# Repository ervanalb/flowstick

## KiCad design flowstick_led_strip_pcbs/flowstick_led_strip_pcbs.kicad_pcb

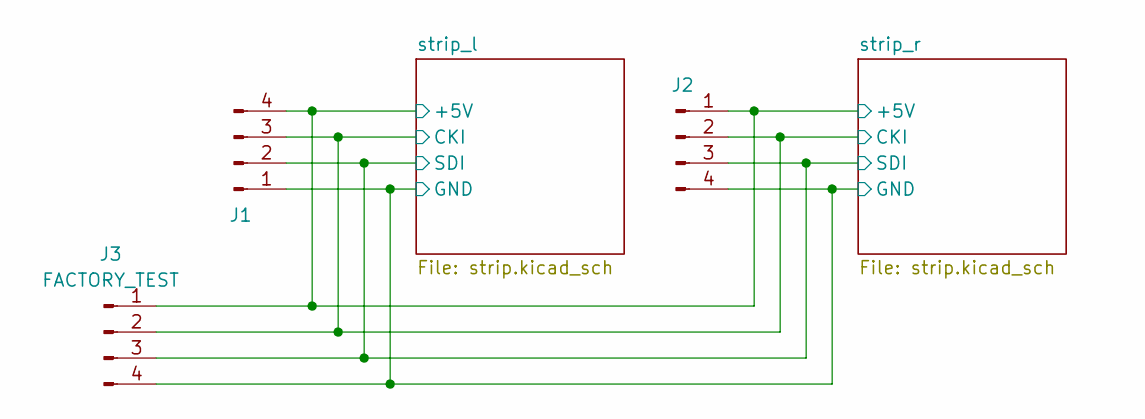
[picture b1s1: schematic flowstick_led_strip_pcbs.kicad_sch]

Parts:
J1, J2: LED; quad_b2b_pad
J3: FACTORY_TEST; PinHeader_1x04_P2.54mm_Vertical

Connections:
/strip_l/+5V: J1.4, J2.1, J3.1; also elsewhere on the board
/strip_l/CKI: J1.3, J2.2, J3.2; also elsewhere on the board
/strip_l/GND: J1.1, J2.4, J3.4; also elsewhere on the board
/strip_l/SDI: J1.2, J2.3, J3.3; also elsewhere on the board

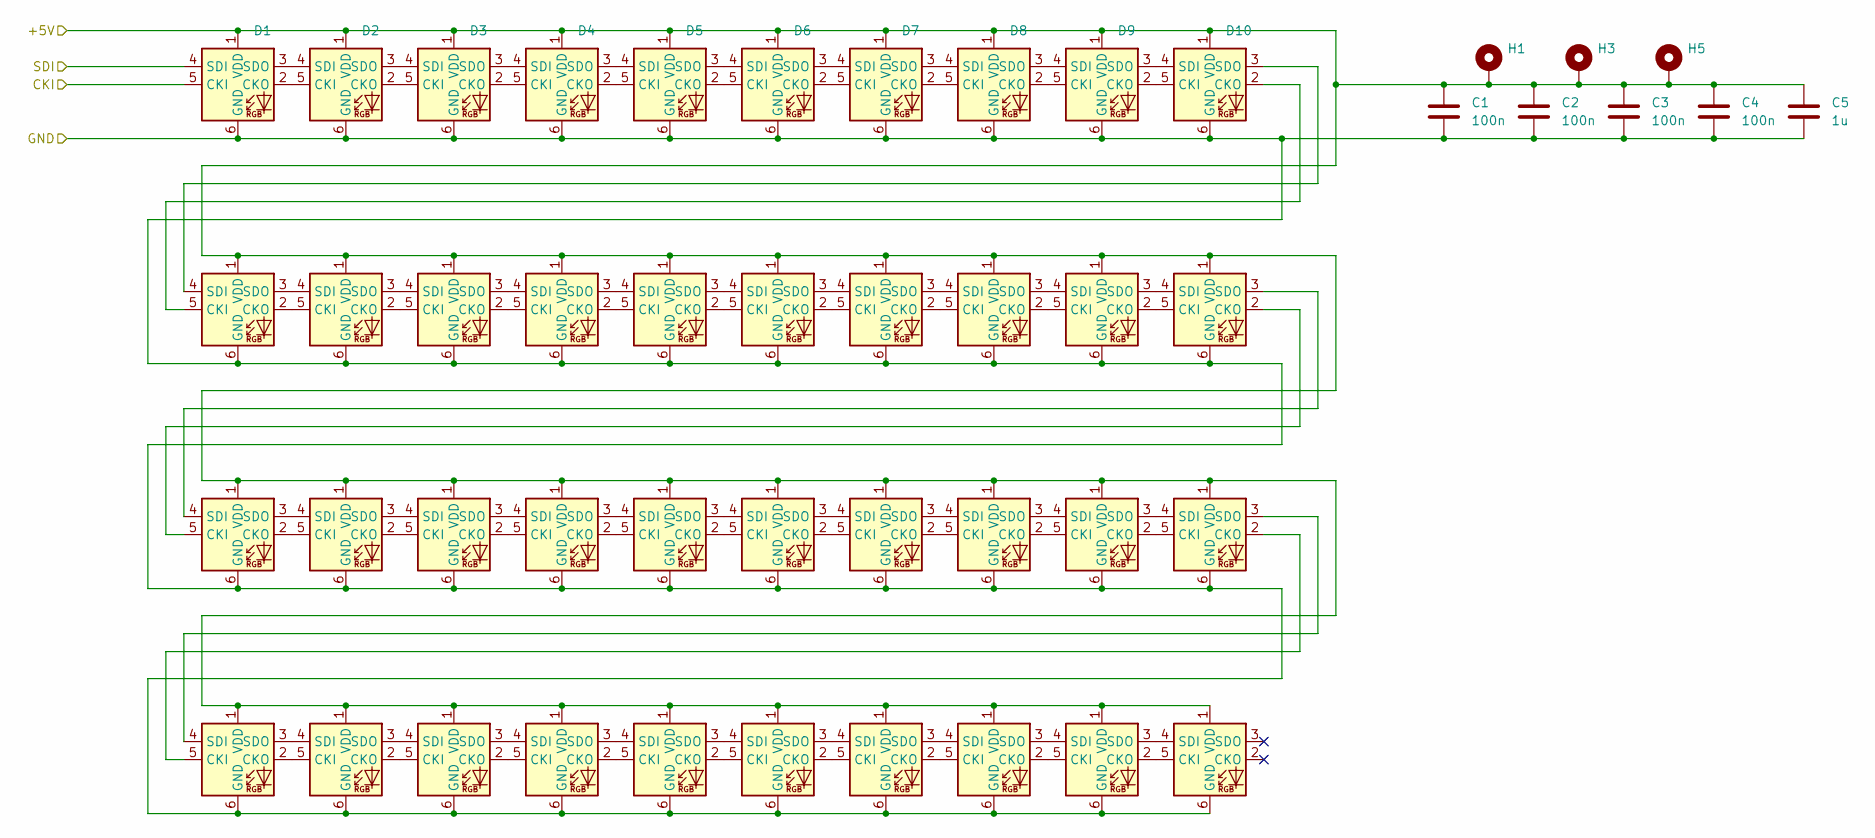
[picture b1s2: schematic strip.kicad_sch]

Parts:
C1, C2, C3, C4: 100n; C_0603_1608Metric
C5: 1u; C_0603_1608Metric
D1, D2, D3, D4, D5, D6, D7, D8, D9, D10, D11, D12, D13, D14, D15, D16, D17, D18, D19, D20, D21, D22, D23, D24, D25, D26, D27, D28, D29, D30, D31, D32, D33, D34, D35, D36, D37, D38, D39, D40: APA102-2020; LED-APA102-2020-6_90deg
H1, H3, H5: MountingHole_Pad; single_b2b_pad_doublewide

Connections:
/strip_l/+5V: C1.1, C2.1, C3.1, C4.1, C5.1, D1.1 (VDD), D2.1 (VDD), D3.1 (VDD), D4.1 (VDD), D5.1 (VDD), D6.1 (VDD), D7.1 (VDD), D8.1 (VDD), D9.1 (VDD), D10.1 (VDD), D11.1 (VDD), D12.1 (VDD), D13.1 (VDD), D14.1 (VDD), D15.1 (VDD), D16.1 (VDD), D17.1 (VDD), D18.1 (VDD), D19.1 (VDD), D20.1 (VDD), D21.1 (VDD), D22.1 (VDD), D23.1 (VDD), D24.1 (VDD), D25.1 (VDD), D26.1 (VDD), D27.1 (VDD), D28.1 (VDD), D29.1 (VDD), D30.1 (VDD), D31.1 (VDD), D32.1 (VDD), D33.1 (VDD), D34.1 (VDD), D35.1 (VDD), D36.1 (VDD), D37.1 (VDD), D38.1 (VDD), D39.1 (VDD), D40.1 (VDD), H1.1, H3.1, H5.1; also elsewhere on the board
/strip_l/CKI: D1.5 (CKI); also elsewhere on the board
/strip_l/GND: C1.2, C2.2, C3.2, C4.2, C5.2, D1.6 (GND), D2.6 (GND), D3.6 (GND), D4.6 (GND), D5.6 (GND), D6.6 (GND), D7.6 (GND), D8.6 (GND), D9.6 (GND), D10.6 (GND), D11.6 (GND), D12.6 (GND), D13.6 (GND), D14.6 (GND), D15.6 (GND), D16.6 (GND), D17.6 (GND), D18.6 (GND), D19.6 (GND), D20.6 (GND), D21.6 (GND), D22.6 (GND), D23.6 (GND), D24.6 (GND), D25.6 (GND), D26.6 (GND), D27.6 (GND), D28.6 (GND), D29.6 (GND), D30.6 (GND), D31.6 (GND), D32.6 (GND), D33.6 (GND), D34.6 (GND), D35.6 (GND), D36.6 (GND), D37.6 (GND), D38.6 (GND), D39.6 (GND), D40.6 (GND); also elsewhere on the board
/strip_l/SDI: D1.4 (SDI); also elsewhere on the board
unnamed: D1.2 (CKO), D2.5 (CKI)
unnamed: D1.3 (SDO), D2.4 (SDI)
unnamed: D2.2 (CKO), D3.5 (CKI)
unnamed: D2.3 (SDO), D3.4 (SDI)
unnamed: D3.2 (CKO), D4.5 (CKI)
unnamed: D3.3 (SDO), D4.4 (SDI)
unnamed: D4.2 (CKO), D5.5 (CKI)
unnamed: D4.3 (SDO), D5.4 (SDI)
unnamed: D5.2 (CKO), D6.5 (CKI)
unnamed: D5.3 (SDO), D6.4 (SDI)
unnamed: D6.2 (CKO), D7.5 (CKI)
unnamed: D6.3 (SDO), D7.4 (SDI)
unnamed: D7.2 (CKO), D8.5 (CKI)
unnamed: D7.3 (SDO), D8.4 (SDI)
unnamed: D8.2 (CKO), D9.5 (CKI)
unnamed: D8.3 (SDO), D9.4 (SDI)
unnamed: D9.2 (CKO), D10.5 (CKI)
unnamed: D10.2 (CKO), D11.5 (CKI)
unnamed: D9.3 (SDO), D10.4 (SDI)
unnamed: D10.3 (SDO), D11.4 (SDI)
unnamed: D11.2 (CKO), D12.5 (CKI)
unnamed: D11.3 (SDO), D12.4 (SDI)
unnamed: D12.2 (CKO), D13.5 (CKI)
unnamed: D12.3 (SDO), D13.4 (SDI)
unnamed: D13.2 (CKO), D14.5 (CKI)
unnamed: D13.3 (SDO), D14.4 (SDI)
unnamed: D14.2 (CKO), D15.5 (CKI)
unnamed: D14.3 (SDO), D15.4 (SDI)
unnamed: D15.2 (CKO), D16.5 (CKI)
unnamed: D15.3 (SDO), D16.4 (SDI)
unnamed: D16.2 (CKO), D17.5 (CKI)
unnamed: D16.3 (SDO), D17.4 (SDI)
unnamed: D17.2 (CKO), D18.5 (CKI)
unnamed: D17.3 (SDO), D18.4 (SDI)
unnamed: D18.2 (CKO), D19.5 (CKI)
unnamed: D18.3 (SDO), D19.4 (SDI)
unnamed: D19.2 (CKO), D20.5 (CKI)
unnamed: D19.3 (SDO), D20.4 (SDI)
unnamed: D20.2 (CKO), D21.5 (CKI)
unnamed: D20.3 (SDO), D21.4 (SDI)
unnamed: D21.2 (CKO), D22.5 (CKI)
unnamed: D21.3 (SDO), D22.4 (SDI)
unnamed: D22.2 (CKO), D23.5 (CKI)
unnamed: D22.3 (SDO), D23.4 (SDI)
unnamed: D23.2 (CKO), D24.5 (CKI)
unnamed: D23.3 (SDO), D24.4 (SDI)
unnamed: D24.2 (CKO), D25.5 (CKI)
unnamed: D24.3 (SDO), D25.4 (SDI)
unnamed: D25.2 (CKO), D26.5 (CKI)
unnamed: D25.3 (SDO), D26.4 (SDI)
unnamed: D26.2 (CKO), D27.5 (CKI)
unnamed: D26.3 (SDO), D27.4 (SDI)
unnamed: D27.2 (CKO), D28.5 (CKI)
unnamed: D27.3 (SDO), D28.4 (SDI)
unnamed: D28.2 (CKO), D29.5 (CKI)
unnamed: D28.3 (SDO), D29.4 (SDI)
unnamed: D29.2 (CKO), D30.5 (CKI)
unnamed: D29.3 (SDO), D30.4 (SDI)
unnamed: D30.2 (CKO), D31.5 (CKI)
unnamed: D30.3 (SDO), D31.4 (SDI)
unnamed: D31.2 (CKO), D32.5 (CKI)
unnamed: D31.3 (SDO), D32.4 (SDI)
unnamed: D32.2 (CKO), D33.5 (CKI)
unnamed: D32.3 (SDO), D33.4 (SDI)
unnamed: D33.2 (CKO), D34.5 (CKI)
unnamed: D33.3 (SDO), D34.4 (SDI)
unnamed: D34.2 (CKO), D35.5 (CKI)
unnamed: D34.3 (SDO), D35.4 (SDI)
unnamed: D35.2 (CKO), D36.5 (CKI)
unnamed: D35.3 (SDO), D36.4 (SDI)
unnamed: D36.2 (CKO), D37.5 (CKI)
unnamed: D36.3 (SDO), D37.4 (SDI)
unnamed: D37.2 (CKO), D38.5 (CKI)
unnamed: D37.3 (SDO), D38.4 (SDI)
unnamed: D38.2 (CKO), D39.5 (CKI)
unnamed: D38.3 (SDO), D39.4 (SDI)
unnamed: D39.2 (CKO), D40.5 (CKI)
unnamed: D39.3 (SDO), D40.4 (SDI)

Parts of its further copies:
C6, C7, C8, C9: 100n; C_0603_1608Metric
C10: 1u; C_0603_1608Metric
D41, D42, D43, D44, D45, D46, D47, D48, D49, D50, D51, D52, D53, D54, D55, D56, D57, D58, D59, D60, D61, D62, D63, D64, D65, D66, D67, D68, D69, D70, D71, D72, D73, D74, D75, D76, D77, D78, D79, D80: APA102-2020; LED-APA102-2020-6_90deg
H2, H4, H6: MountingHole_Pad; single_b2b_pad_doublewide

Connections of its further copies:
/strip_l/+5V: C6.1, C7.1, C8.1, C9.1, C10.1, D41.1 (VDD), D42.1 (VDD), D43.1 (VDD), D44.1 (VDD), D45.1 (VDD), D46.1 (VDD), D47.1 (VDD), D48.1 (VDD), D49.1 (VDD), D50.1 (VDD), D51.1 (VDD), D52.1 (VDD), D53.1 (VDD), D54.1 (VDD), D55.1 (VDD), D56.1 (VDD), D57.1 (VDD), D58.1 (VDD), D59.1 (VDD), D60.1 (VDD), D61.1 (VDD), D62.1 (VDD), D63.1 (VDD), D64.1 (VDD), D65.1 (VDD), D66.1 (VDD), D67.1 (VDD), D68.1 (VDD), D69.1 (VDD), D70.1 (VDD), D71.1 (VDD), D72.1 (VDD), D73.1 (VDD), D74.1 (VDD), D75.1 (VDD), D76.1 (VDD), D77.1 (VDD), D78.1 (VDD), D79.1 (VDD), D80.1 (VDD), H2.1, H4.1, H6.1; also elsewhere on the board
/strip_l/CKI: D41.5 (CKI); also elsewhere on the board
/strip_l/GND: C6.2, C7.2, C8.2, C9.2, C10.2, D41.6 (GND), D42.6 (GND), D43.6 (GND), D44.6 (GND), D45.6 (GND), D46.6 (GND), D47.6 (GND), D48.6 (GND), D49.6 (GND), D50.6 (GND), D51.6 (GND), D52.6 (GND), D53.6 (GND), D54.6 (GND), D55.6 (GND), D56.6 (GND), D57.6 (GND), D58.6 (GND), D59.6 (GND), D60.6 (GND), D61.6 (GND), D62.6 (GND), D63.6 (GND), D64.6 (GND), D65.6 (GND), D66.6 (GND), D67.6 (GND), D68.6 (GND), D69.6 (GND), D70.6 (GND), D71.6 (GND), D72.6 (GND), D73.6 (GND), D74.6 (GND), D75.6 (GND), D76.6 (GND), D77.6 (GND), D78.6 (GND), D79.6 (GND), D80.6 (GND); also elsewhere on the board
/strip_l/SDI: D41.4 (SDI); also elsewhere on the board
unnamed: D41.2 (CKO), D42.5 (CKI)
unnamed: D41.3 (SDO), D42.4 (SDI)
unnamed: D42.2 (CKO), D43.5 (CKI)
unnamed: D42.3 (SDO), D43.4 (SDI)
unnamed: D43.2 (CKO), D44.5 (CKI)
unnamed: D43.3 (SDO), D44.4 (SDI)
unnamed: D44.2 (CKO), D45.5 (CKI)
unnamed: D44.3 (SDO), D45.4 (SDI)
unnamed: D45.2 (CKO), D46.5 (CKI)
unnamed: D45.3 (SDO), D46.4 (SDI)
unnamed: D46.2 (CKO), D47.5 (CKI)
unnamed: D46.3 (SDO), D47.4 (SDI)
unnamed: D47.2 (CKO), D48.5 (CKI)
unnamed: D47.3 (SDO), D48.4 (SDI)
unnamed: D48.2 (CKO), D49.5 (CKI)
unnamed: D48.3 (SDO), D49.4 (SDI)
unnamed: D49.2 (CKO), D50.5 (CKI)
unnamed: D49.3 (SDO), D50.4 (SDI)
unnamed: D50.2 (CKO), D51.5 (CKI)
unnamed: D50.3 (SDO), D51.4 (SDI)
unnamed: D51.2 (CKO), D52.5 (CKI)
unnamed: D51.3 (SDO), D52.4 (SDI)
unnamed: D52.2 (CKO), D53.5 (CKI)
unnamed: D52.3 (SDO), D53.4 (SDI)
unnamed: D53.2 (CKO), D54.5 (CKI)
unnamed: D53.3 (SDO), D54.4 (SDI)
unnamed: D54.2 (CKO), D55.5 (CKI)
unnamed: D54.3 (SDO), D55.4 (SDI)
unnamed: D55.2 (CKO), D56.5 (CKI)
unnamed: D55.3 (SDO), D56.4 (SDI)
unnamed: D56.2 (CKO), D57.5 (CKI)
unnamed: D56.3 (SDO), D57.4 (SDI)
unnamed: D57.2 (CKO), D58.5 (CKI)
unnamed: D57.3 (SDO), D58.4 (SDI)
unnamed: D58.2 (CKO), D59.5 (CKI)
unnamed: D58.3 (SDO), D59.4 (SDI)
unnamed: D59.2 (CKO), D60.5 (CKI)
unnamed: D59.3 (SDO), D60.4 (SDI)
unnamed: D60.2 (CKO), D61.5 (CKI)
unnamed: D60.3 (SDO), D61.4 (SDI)
unnamed: D61.2 (CKO), D62.5 (CKI)
unnamed: D61.3 (SDO), D62.4 (SDI)
unnamed: D62.2 (CKO), D63.5 (CKI)
unnamed: D62.3 (SDO), D63.4 (SDI)
unnamed: D63.2 (CKO), D64.5 (CKI)
unnamed: D63.3 (SDO), D64.4 (SDI)
unnamed: D64.2 (CKO), D65.5 (CKI)
unnamed: D64.3 (SDO), D65.4 (SDI)
unnamed: D65.2 (CKO), D66.5 (CKI)
unnamed: D65.3 (SDO), D66.4 (SDI)
unnamed: D66.2 (CKO), D67.5 (CKI)
unnamed: D66.3 (SDO), D67.4 (SDI)
unnamed: D67.2 (CKO), D68.5 (CKI)
unnamed: D67.3 (SDO), D68.4 (SDI)
unnamed: D68.2 (CKO), D69.5 (CKI)
unnamed: D68.3 (SDO), D69.4 (SDI)
unnamed: D69.2 (CKO), D70.5 (CKI)
unnamed: D69.3 (SDO), D70.4 (SDI)
unnamed: D70.2 (CKO), D71.5 (CKI)
unnamed: D70.3 (SDO), D71.4 (SDI)
unnamed: D71.2 (CKO), D72.5 (CKI)
unnamed: D71.3 (SDO), D72.4 (SDI)
unnamed: D72.2 (CKO), D73.5 (CKI)
unnamed: D72.3 (SDO), D73.4 (SDI)
unnamed: D73.2 (CKO), D74.5 (CKI)
unnamed: D73.3 (SDO), D74.4 (SDI)
unnamed: D74.2 (CKO), D75.5 (CKI)
unnamed: D74.3 (SDO), D75.4 (SDI)
unnamed: D75.2 (CKO), D76.5 (CKI)
unnamed: D75.3 (SDO), D76.4 (SDI)
unnamed: D76.2 (CKO), D77.5 (CKI)
unnamed: D76.3 (SDO), D77.4 (SDI)
unnamed: D77.2 (CKO), D78.5 (CKI)
unnamed: D77.3 (SDO), D78.4 (SDI)
unnamed: D78.2 (CKO), D79.5 (CKI)
unnamed: D78.3 (SDO), D79.4 (SDI)
unnamed: D79.2 (CKO), D80.5 (CKI)
unnamed: D79.3 (SDO), D80.4 (SDI)

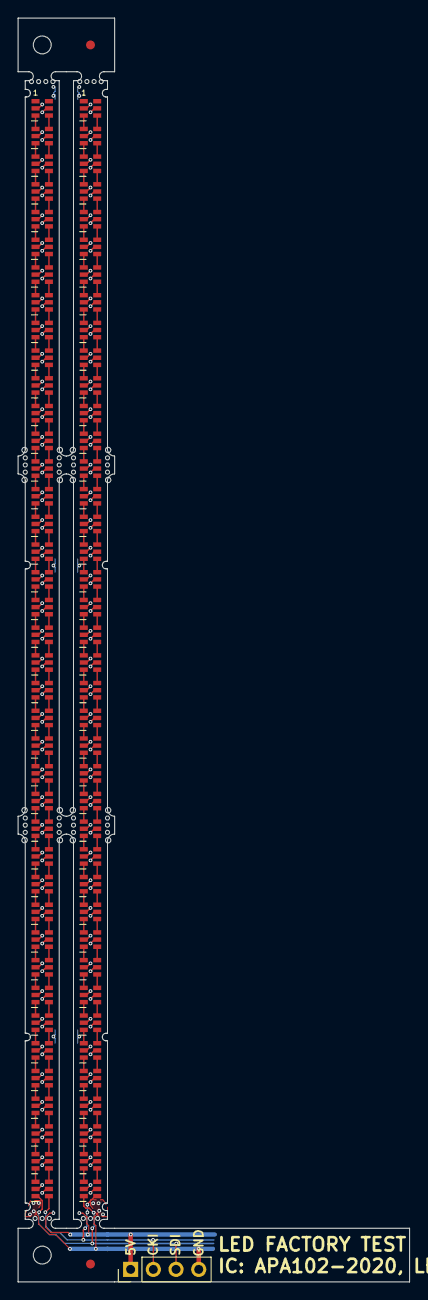
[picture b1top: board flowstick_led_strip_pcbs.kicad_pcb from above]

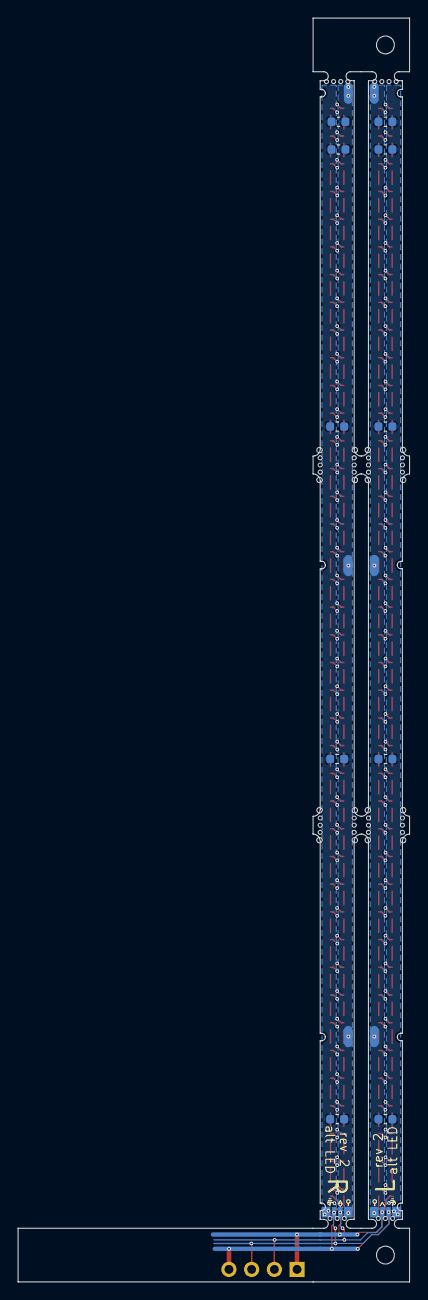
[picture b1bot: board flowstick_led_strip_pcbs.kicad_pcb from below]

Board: 2 copper layers, 43.8 x 141.4 mm, 99 parts (18 on the bottom side), 160 nets.

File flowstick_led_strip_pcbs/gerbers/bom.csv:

Designator,Quantity,Value,Footprint,Manufacturer,Part Number,JLCPCB Part #
"C1,C2,C3,C4,C6,C7,C8,C9",64,100n,Capacitor_SMD:C_0603_1608Metric,,,C14663
"C5,C10",16,1u,Capacitor_SMD:C_0603_1608Metric,,,C106248
"D1,D2,D3,D4,D5,D6,D7,D8,D9,D10,D11,D12,D13,D14,D15,D16,D17,D18,D19,D20,D21,D22,D23,D24,D25,D26,D27,D28,D29,D30,D31,D32,D33,D34,D35,D36,D37,D38,D39,D40,D41,D42,D43,D44,D45,D46,D47,D48,D49,D50,D51,D52,D53,D54,D55,D56,D57,D58,D59,D60,D61,D62,D63,D64,D65,D66,D67,D68,D69,D70,D71,D72,D73,D74,D75,D76,D77,D78,D79,D80",640,APA102-2020,LED_SMD:LED-APA102-2020,APA Electronics,APA102-2020,C22439302

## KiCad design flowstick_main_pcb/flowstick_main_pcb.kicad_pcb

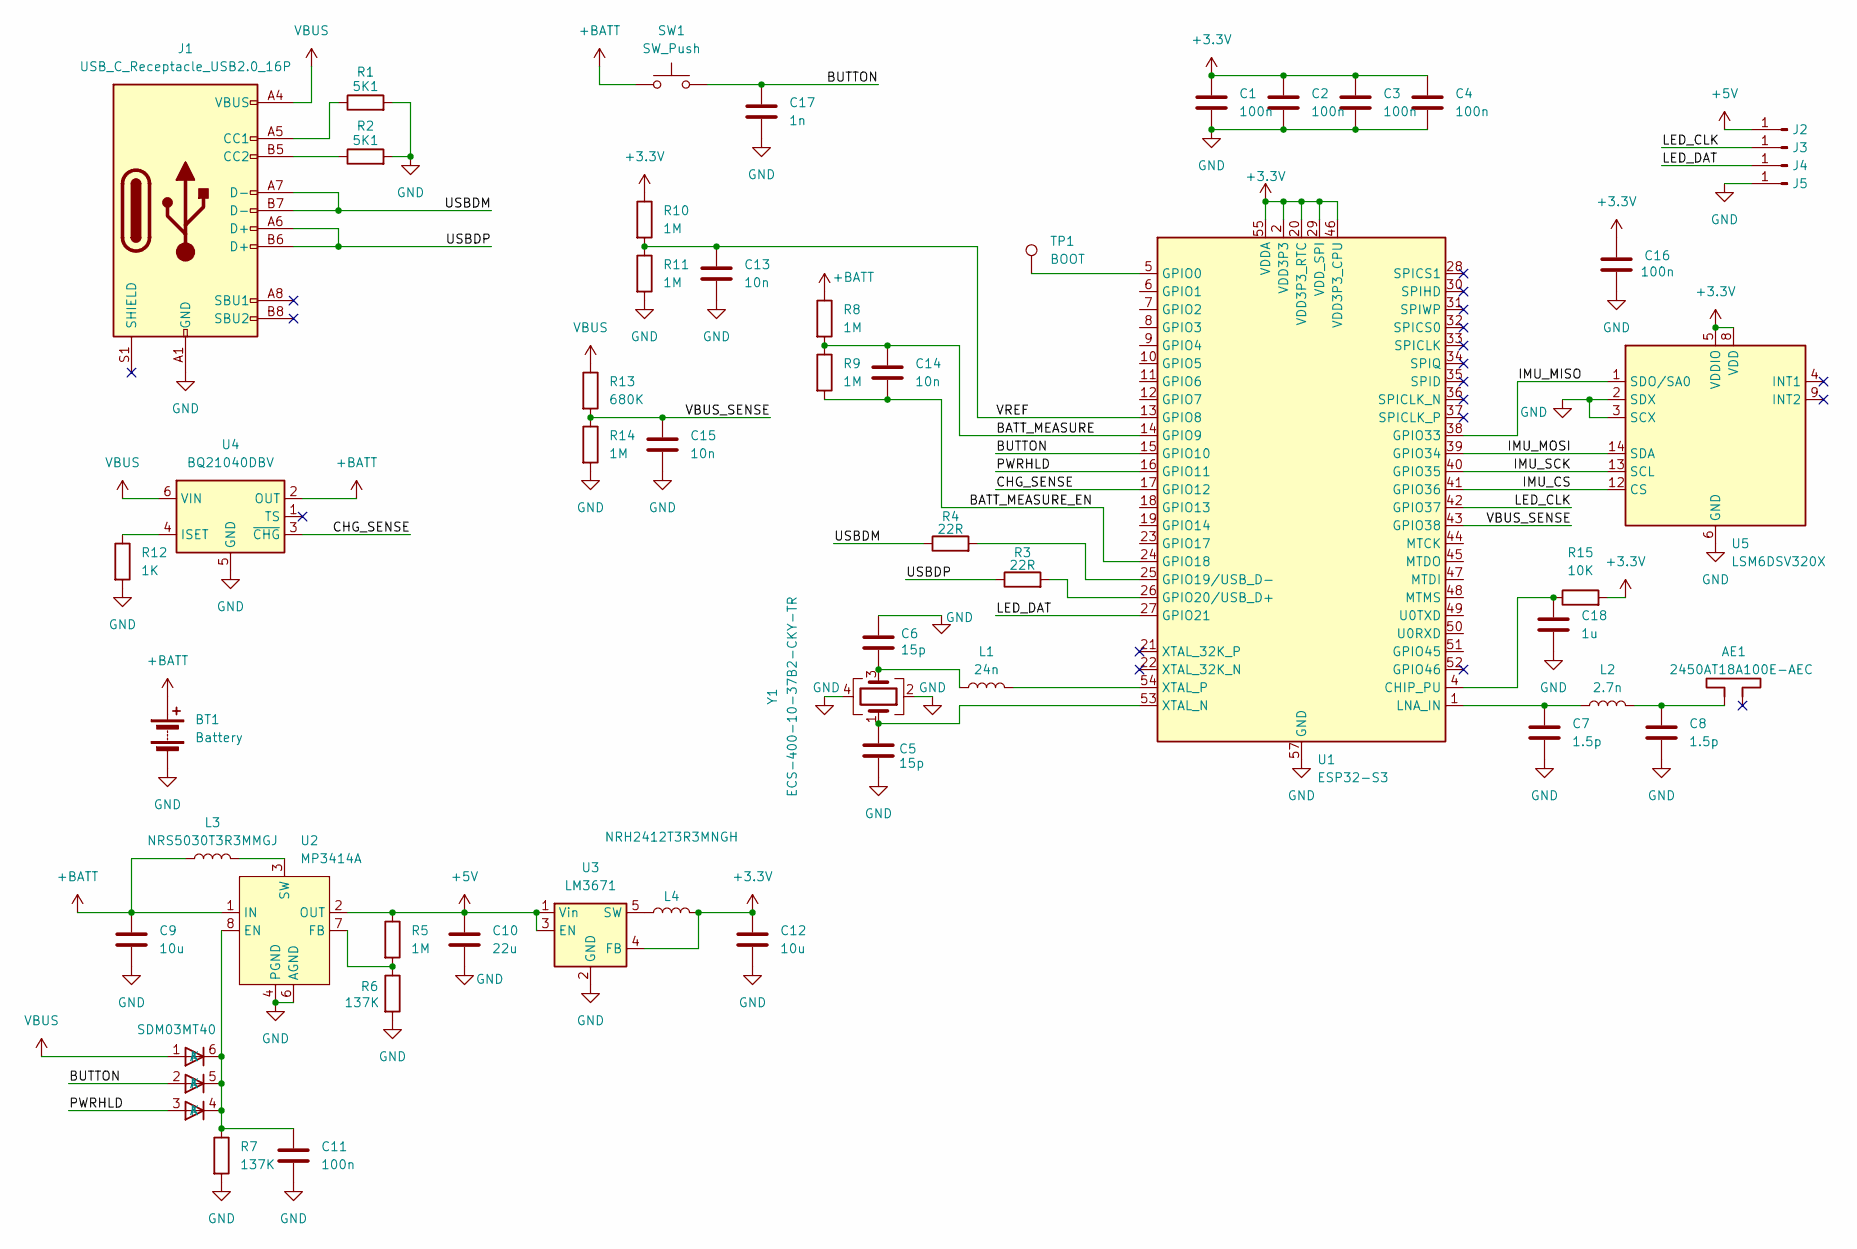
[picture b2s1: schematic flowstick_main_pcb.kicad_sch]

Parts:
AE1: 2450AT18A100E-AEC; R_1206_3216Metric
BT1: Battery; PinHeader_1x02_P2.54mm_Vertical
C1, C2, C3, C4, C16: 100n; C_0402_1005Metric
C5, C6: 15p; C_0201_0603Metric
C7, C8: 1.5p; C_0201_0603Metric
C9, C12: 10u; C_1206_3216Metric
C10: 22u; C_1206_3216Metric
C11: 100n; C_0201_0603Metric
C13, C14, C15: 10n; C_0201_0603Metric
C17: 1n; C_0201_0603Metric
C18: 1u; C_0201_0603Metric
D1: SDM03MT40; SOT-23-6
J1: USB_C_Receptacle_USB2.0_16P; USB_C_Receptacle_GCT_USB4105-xx-A_16P_TopMnt_Horizontal
J2, J3, J4, J5: Conn_01x01_Pin; Untitled
L1: 24n; L_0201_0603Metric
L2: 2.7n; L_0201_0603Metric
L3: NRS5030T3R3MMGJ; L_Taiyo-Yuden_NR-50xx
L4: NRH2412T3R3MNGH; L_Taiyo-Yuden_NR-24xx
R1, R2: 5K1; C_0201_0603Metric
R3, R4: 22R; C_0201_0603Metric
R5, R8, R9, R10, R11, R14: 1M; C_0201_0603Metric
R6, R7: 137K; C_0201_0603Metric
R12: 1K; C_0201_0603Metric
R13: 680K; C_0201_0603Metric
R15: 10K; R_0201_0603Metric
SW1: SW_Push; SW_SPST_EVQP7C
TP1: BOOT; TestPoint_Pad_D1.0mm
U1: ESP32-S3; QFN-56-1EP_7x7mm_P0.4mm_EP4x4mm
U2: MP3414A; TSOT-23-8
U3: LM3671; TSOT-23-5
U4: BQ21040DBV; SOT-23-6
U5: LSM6DSV320X; LGA-14_3x2.5mm_P0.5mm_LayoutBorder3x4y
Y1: ECS-400-10-37B2-CKY-TR; Crystal_SMD_2016-4Pin_2.0x1.6mm

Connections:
+3.3V: C1.1, C2.1, C3.1, C4.1, C12.1, C16.1, L4.2, R10.1, R15.2, U1.2 (VDD3P3), U1.3 (VDD3P3), U1.20 (VDD3P3_RTC), U1.29 (VDD_SPI), U1.46 (VDD3P3_CPU), U1.55 (VDDA), U1.56 (VDDA), U3.4 (FB), U5.5 (VDDIO), U5.8 (VDD)
+5V: C10.1, J2.1, R5.1, U2.2 (OUT), U3.1 (Vin), U3.3 (EN)
+BATT: BT1.1 (+), C9.1, L3.1, R8.1, SW1.1, U2.1 (IN), U4.2 (OUT)
/BATT_MEASURE: C14.1, R8.2, R9.1, U1.14 (GPIO9)
/BATT_MEASURE_EN: C14.2, R9.2, U1.24 (GPIO18)
/BUTTON: C17.1, D1.2 (A), SW1.2, U1.15 (GPIO10)
/CHG_SENSE: U1.17 (GPIO12), U4.3 (~CHG)
/IMU_CS: U1.41 (GPIO36), U5.12 (CS)
/IMU_PICO: U1.38 (GPIO33), U5.1 (SDO/SA0)
/IMU_POCI: U1.39 (GPIO34), U5.14 (SDA)
/IMU_SCK: U1.40 (GPIO35), U5.13 (SCL)
/LED_CLK: J3.1, U1.42 (GPIO37)
/LED_DAT: J4.1, U1.27 (GPIO21)
/PWRHLD: D1.3 (A), U1.16 (GPIO11)
/USBDM: J1.A7 (D-), J1.B7 (D-), R4.1
/USBDP: J1.A6 (D+), J1.B6 (D+), R3.1
/VBUS_SENSE: C15.1, R13.2, R14.1, U1.43 (GPIO38)
/VREF: C13.1, R10.2, R11.1, U1.13 (GPIO8)
GND: BT1.2 (-), C1.2, C2.2, C3.2, C4.2, C5.2, C6.1, C7.2, C8.2, C9.2, C10.2, C11.2, C12.2, C13.2, C15.2, C16.2, C17.2, C18.2, J1.A1 (GND), J1.A12 (GND), J1.B1 (GND), J1.B12 (GND), J5.1, R1.2, R2.2, R6.2, R7.2, R11.2, R12.2, R14.2, U1.57 (GND), U2.4 (PGND), U2.6 (AGND), U3.2 (GND), U4.5 (GND), U5.2 (SDX), U5.3 (SCX), U5.6 (GND), U5.7 (GND), Y1.2, Y1.4
unnamed: AE1.1, C8.1, L2.2
unnamed: C6.2, L1.1, Y1.3
unnamed: C11.1, D1.4 (K), D1.5 (K), D1.6 (K), R7.1, U2.8 (EN)
unnamed: J1.A5 (CC1), R1.1
unnamed: J1.B5 (CC2), R2.1
unnamed: C18.1, R15.1, U1.4 (CHIP_PU)
unnamed: TP1.1, U1.5 (GPIO0)
unnamed: R4.2, U1.25 (GPIO19/USB_D-)
unnamed: R3.2, U1.26 (GPIO20/USB_D+)
unnamed: C7.1, L2.1, U1.1 (LNA_IN)
unnamed: C5.1, U1.53 (XTAL_N), Y1.1
unnamed: L1.2, U1.54 (XTAL_P)
unnamed: R5.2, R6.1, U2.7 (FB)
unnamed: L3.2, U2.3 (SW)
unnamed: L4.1, U3.5 (SW)
unnamed: R12.1, U4.4 (ISET)
VBUS: D1.1 (A), J1.A4 (VBUS), J1.A9 (VBUS), J1.B4 (VBUS), J1.B9 (VBUS), R13.1, U4.6 (VIN)

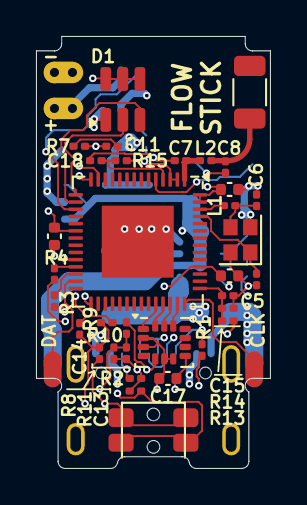
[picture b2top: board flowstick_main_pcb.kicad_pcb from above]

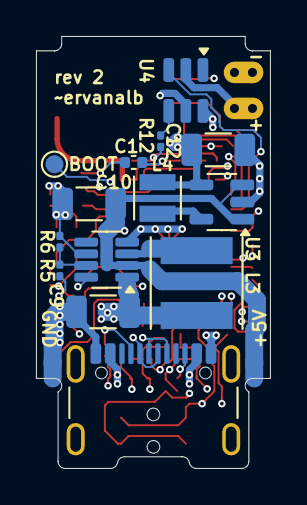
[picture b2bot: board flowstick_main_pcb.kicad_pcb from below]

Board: 4 copper layers, 13.0 x 24.0 mm, 53 parts (16 on the bottom side), 36 nets.

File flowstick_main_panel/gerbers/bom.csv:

Designator,Quantity,Value,Footprint,Manufacturer,Part Number,JLCPCB Part #
AE1,4,,Resistor_SMD:R_1206_3216Metric,Johanson Technology,2450AT18A100E-AEC,C89334
"C1,C2,C3,C4,C16",20,100n,Capacitor_SMD:C_0402_1005Metric,,,C1525
"C5,C6",8,15p,Capacitor_SMD:C_0201_0603Metric,,,C64554
"C7,C8",8,1.5p,Capacitor_SMD:C_0201_0603Metric,,,C50389
"C9,C12",8,10u,Capacitor_SMD:C_1206_3216Metric,,,C319199
C10,4,22u,Capacitor_SMD:C_1206_3216Metric,,,C386064
C11,4,100n,Capacitor_SMD:C_0201_0603Metric,,,C284966
"C13,C14,C15",12,10n,Capacitor_SMD:C_0201_0603Metric,,,C43380
C17,4,1n,Capacitor_SMD:C_0201_0603Metric,,,C66942
C18,4,1u,Capacitor_SMD:C_0201_0603Metric,,,C53067
D1,4,,Package_TO_SOT_SMD:SOT-23-6,Diodes Incorporated,SDM03MT40,C526762
J1,4,USB_C_Receptacle_USB2.0_16P,Connector_USB:USB_C_Receptacle_GCT_USB4105-xx-A_16P_TopMnt_Horizontal,GCT,USB4105-GF-A,C3020560
L1,4,24n,Inductor_SMD:L_0201_0603Metric,,,C206441
L2,4,2.7n,Inductor_SMD:L_0201_0603Metric,,,C76751
L3,4,3u3,Inductor_SMD:L_Taiyo-Yuden_NR-50xx,Taiyo Yuden,NRS5030T3R3MMGJ,C222937
L4,4,3u3,Inductor_SMD:L_Taiyo-Yuden_NR-24xx,Taiyo Yuden,NRH2412T3R3MNGH,C222843
"R1,R2",8,5K1,Capacitor_SMD:C_0201_0603Metric,,,C226588
"R3,R4",8,22R,Capacitor_SMD:C_0201_0603Metric,,,C155743
"R5,R8,R9,R10,R11,R14",24,1M,Capacitor_SMD:C_0201_0603Metric,,,C226459
"R6,R7",8,137K,Capacitor_SMD:C_0201_0603Metric,,,C473623
R12,4,1K,Capacitor_SMD:C_0201_0603Metric,,,C138165
R13,4,680K,Capacitor_SMD:C_0201_0603Metric,,,C473493
R15,4,10K,Resistor_SMD:R_0201_0603Metric,,,C106225
SW1,4,,Button_Switch_SMD:SW_SPST_EVQP7C,Panasonic,EVQ-P7C01P,C388883
U1,4,,Package_DFN_QFN:QFN-56-1EP_7x7mm_P0.4mm_EP4x4mm,Espressif,ESP32-S3FH4R2,C3013940
U2,4,,Package_TO_SOT_SMD:TSOT-23-8,Monolithic Power Systems,MP3414AGJ-Z,C111682
U3,4,3V3,Package_TO_SOT_SMD:TSOT-23-5,Texas Instruments,LM3671MFX-3.3/NOPB,C201586
U4,4,,Package_TO_SOT_SMD:SOT-23-6,Texas Instruments,BQ21040DBV,C78978
U5,4,,Package_LGA:LGA-14_3x2.5mm_P0.5mm_LayoutBorder3x4y,STMicroelectronics,LSM6DSV320X,C26633007
Y1,4,40M,Crystal:Crystal_SMD_2016-4Pin_2.0x1.6mm,ECS,ECS-400-10-37B2-CKY-TR,C5371760

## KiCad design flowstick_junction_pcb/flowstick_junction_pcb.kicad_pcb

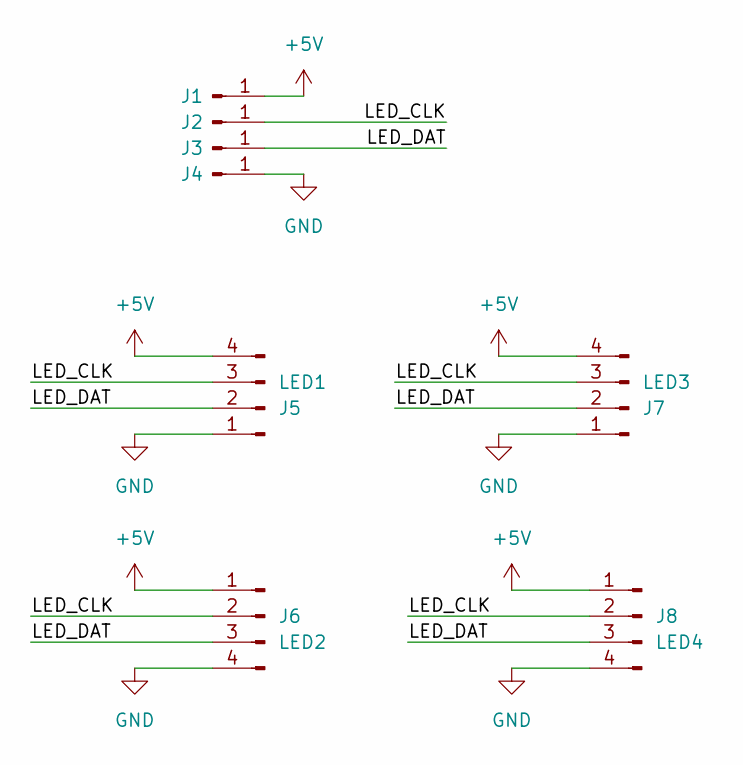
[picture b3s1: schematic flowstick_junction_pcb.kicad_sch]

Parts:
J1, J2, J3, J4: Conn_01x01_Pin; single_b2b_pad
J5: LED1; quad_b2b_pad
J6: LED2; quad_b2b_pad
J7: LED3; quad_b2b_pad
J8: LED4; quad_b2b_pad

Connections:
+5V: J1.1, J5.4, J6.1, J7.4, J8.1
/LED_CLK: J2.1, J5.3, J6.2, J7.3, J8.2
/LED_DAT: J3.1, J5.2, J6.3, J7.2, J8.3
GND: J4.1, J5.1, J6.4, J7.1, J8.4

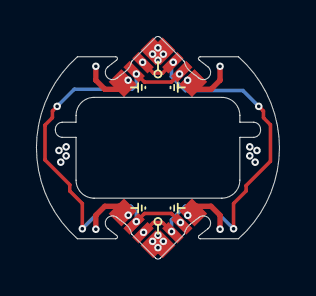
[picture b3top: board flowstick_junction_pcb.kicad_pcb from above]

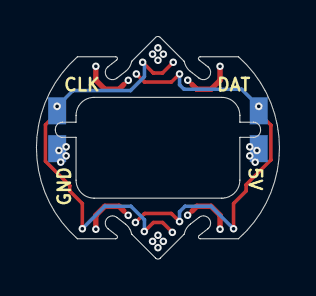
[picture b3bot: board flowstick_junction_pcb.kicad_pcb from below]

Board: 4 copper layers, 13.5 x 12.4 mm, 8 parts (4 on the bottom side), 4 nets.

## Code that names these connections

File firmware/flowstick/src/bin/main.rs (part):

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}

pub struct LedHardware {
    dat: peripherals::GPIO21<'static>,
    clk: peripherals::GPIO37<'static>,
    spi: peripherals::SPI3<'static>,
    i2s: peripherals::I2S0<'static>,
    dma: peripherals::DMA_CH0<'static>,
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}

struct ControlDriver {
    pwrhld: gpio::Output<'static>,
    button: gpio::Input<'static>,
    vbus_sense: gpio::Input<'static>,
    _chg_sense: gpio::Input<'static>,
    adc: analog::adc::Adc<'static, peripherals::ADC1<'static>, Blocking>,
    batt_measure: analog::adc::AdcPin<
        peripherals::GPIO9<'static>,
        peripherals::ADC1<'static>,
        analog::adc::AdcCalCurve<peripherals::ADC1<'static>>,
    >,
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    esp_rtos::start(timg0.timer0);

    // Peripherals
    let pwrhld = gpio::Output::new(
        peripherals.GPIO11,
        gpio::Level::Low,
        gpio::OutputConfig::default(),
    );
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    // BATT_MEASURE_EN
    // This line should be held low always
    gpio::Output::new(
        peripherals.GPIO18,
        gpio::Level::Low,
        gpio::OutputConfig::default(),
    );
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    */

    let mut button = gpio::Input::new(
        peripherals.GPIO10,
        gpio::InputConfig::default().with_pull(gpio::Pull::Down),
    );
    button
        .wakeup_enable(true, gpio::WakeEvent::HighLevel)
        .unwrap();

    let vbus_sense = gpio::Input::new(peripherals.GPIO38, gpio::InputConfig::default());
    let _chg_sense = gpio::Input::new(
        peripherals.GPIO12,
        gpio::InputConfig::default().with_pull(gpio::Pull::Up),
    );

    // ADC for battery reading
    let mut adc_config = analog::adc::AdcConfig::new();
    let batt_measure = adc_config
        .enable_pin_with_cal::<peripherals::GPIO9<'_>, analog::adc::AdcCalCurve<_>>(
            peripherals.GPIO9,
            analog::adc::Attenuation::_11dB,
        );
    let adc = analog::adc::Adc::new(peripherals.ADC1, adc_config);
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            .with_mode(spi::Mode::_0),
    )
    .unwrap()
    .with_miso(peripherals.GPIO33)
    .with_mosi(peripherals.GPIO34)
    .with_sck(peripherals.GPIO35)
    .with_cs(peripherals.GPIO36);

    let button_press_timestamp = rtc.time_since_boot();

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            button_longpress_active: button_held_through_sw_reset,
        },
        LedHardware {
            dat: peripherals.GPIO21,
            clk: peripherals.GPIO37,
            spi: peripherals.SPI3,
            i2s: peripherals.I2S0,
            dma: peripherals.DMA_CH0,
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
    fn read_battery_voltage(&mut self) -> Option<u16> {
        const ADC_SAMPLES: u32 = 32;
        let mut batt_measure: u32 = 0;
        for _ in 0..ADC_SAMPLES {
            let reading = self.adc.read_blocking(&mut self.batt_measure);
            if reading < 400 || reading > 3700 {
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
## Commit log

2025-07-17 Add rev1 PCB designs
2025-07-18 Add hello world firmware program
2025-07-18 Fix logging, add simple color fade test
2025-07-25 Add start of a mobile app
2025-07-29 Color fade firmware
2025-07-29 Get BT scan working on android
2025-07-30 Use I2S + DMA to send LED animations
2025-07-30 add SPI
2025-08-01 ADC for battery & SPI for IMU
2025-08-06 work on rev2 + panelize LED strips
2025-08-07 Final rev2, probably
2025-08-11 Hardware rev2 including 6-pin version of LED strip boards. Firmware: begin to integrate embassy, switch LED drivers between low- and high-power
2025-08-12 start work on bluetooth
2025-08-13 Switch to trouble, test out BLE scan
2025-08-13 Add BLE advertising
2025-08-19 Update LED strips to use to 6-pin LED package
2025-08-19 Add LED package with alternate pinout
2025-08-19 Switch to 90 degree alternate LED pinout
2025-08-22 Add exemplary drawings for factory
2025-09-06 brownout testing
2025-09-06 apa102 factory test
2025-09-22 implement CRDT for bluetooth syncing
2025-09-22 Add ability to cycle through patterns, and remove commented code
2025-09-22 Add build script to convert PNGs, and add test pattern
2025-09-23 Add patterns, remove logging (caused crashes when sleeping)
2025-09-25 play with deep sleep for charging
2025-09-26 Fix up deep sleep for charging mode, add more patterns
2025-10-03 Improved battery charging logic -- 3 second deep sleep + 300ms keep awake + fixed animation timing + fixed ADC reading
2025-10-08 Accurate battery meter on power-off
2025-10-09 New charging animation & behavior (no sleep)
2025-10-10 Read from IMU
